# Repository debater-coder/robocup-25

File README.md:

# Robocup 2025

- `./pico/` -- use rshell to copy contents of `./pico/` to the Raspberry Pi Pico running MicroPython
- `./simulator/` -- bevy rust project. Dependencies are listed in `./shell.nix` (excluding rust/cargo)

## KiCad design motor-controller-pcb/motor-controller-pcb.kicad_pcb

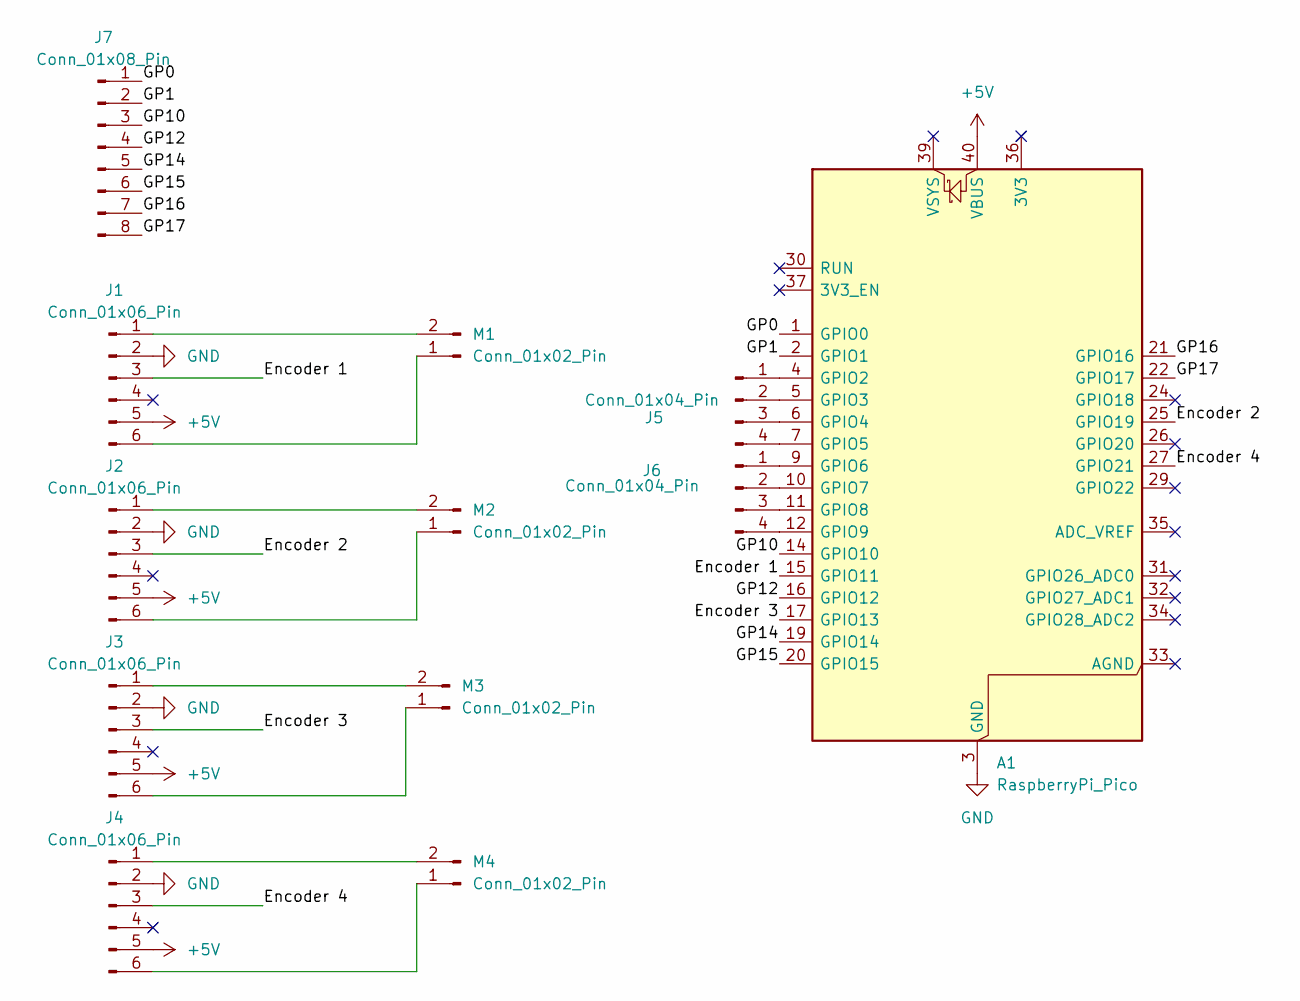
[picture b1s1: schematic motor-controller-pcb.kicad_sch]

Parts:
A1: RaspberryPi_Pico; RaspberryPi_Pico_Common_Unspecified
J1, J2, J3, J4: Conn_01x06_Pin; PinHeader_1x06_P2.54mm_Vertical
J5, J6: Conn_01x04_Pin; PinHeader_1x04_P2.54mm_Vertical
J7: Conn_01x08_Pin; PinHeader_1x08_P2.54mm_Vertical
M1, M2, M3, M4: Conn_01x02_Pin; PinHeader_1x02_P2.54mm_Vertical

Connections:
+5V: A1.40 (VBUS), J1.5, J2.5, J3.5, J4.5
/Encoder 1: A1.15 (GPIO11), J1.3
/Encoder 2: A1.25 (GPIO19), J2.3
/Encoder 3: A1.17 (GPIO13), J3.3
/Encoder 4: A1.27 (GPIO21), J4.3
/GP0: A1.1 (GPIO0), J7.1
/GP1: A1.2 (GPIO1), J7.2
/GP10: A1.14 (GPIO10), J7.3
/GP12: A1.16 (GPIO12), J7.4
/GP14: A1.19 (GPIO14), J7.5
/GP15: A1.20 (GPIO15), J7.6
/GP16: A1.21 (GPIO16), J7.7
/GP17: A1.22 (GPIO17), J7.8
GND: A1.3 (GND), A1.8 (GND), A1.13 (GND), A1.18 (GND), A1.23 (GND), A1.28 (GND), A1.38 (GND), J1.2, J2.2, J3.2, J4.2
unnamed: A1.4 (GPIO2), J5.1
unnamed: A1.5 (GPIO3), J5.2
unnamed: A1.6 (GPIO4), J5.3
unnamed: A1.7 (GPIO5), J5.4
unnamed: A1.9 (GPIO6), J6.1
unnamed: A1.10 (GPIO7), J6.2
unnamed: A1.11 (GPIO8), J6.3
unnamed: A1.12 (GPIO9), J6.4
unnamed: J1.1, M1.2
unnamed: J1.6, M1.1
unnamed: J2.1, M2.2
unnamed: J2.6, M2.1
unnamed: J3.1, M3.2
unnamed: J3.6, M3.1
unnamed: J4.1, M4.2
unnamed: J4.6, M4.1

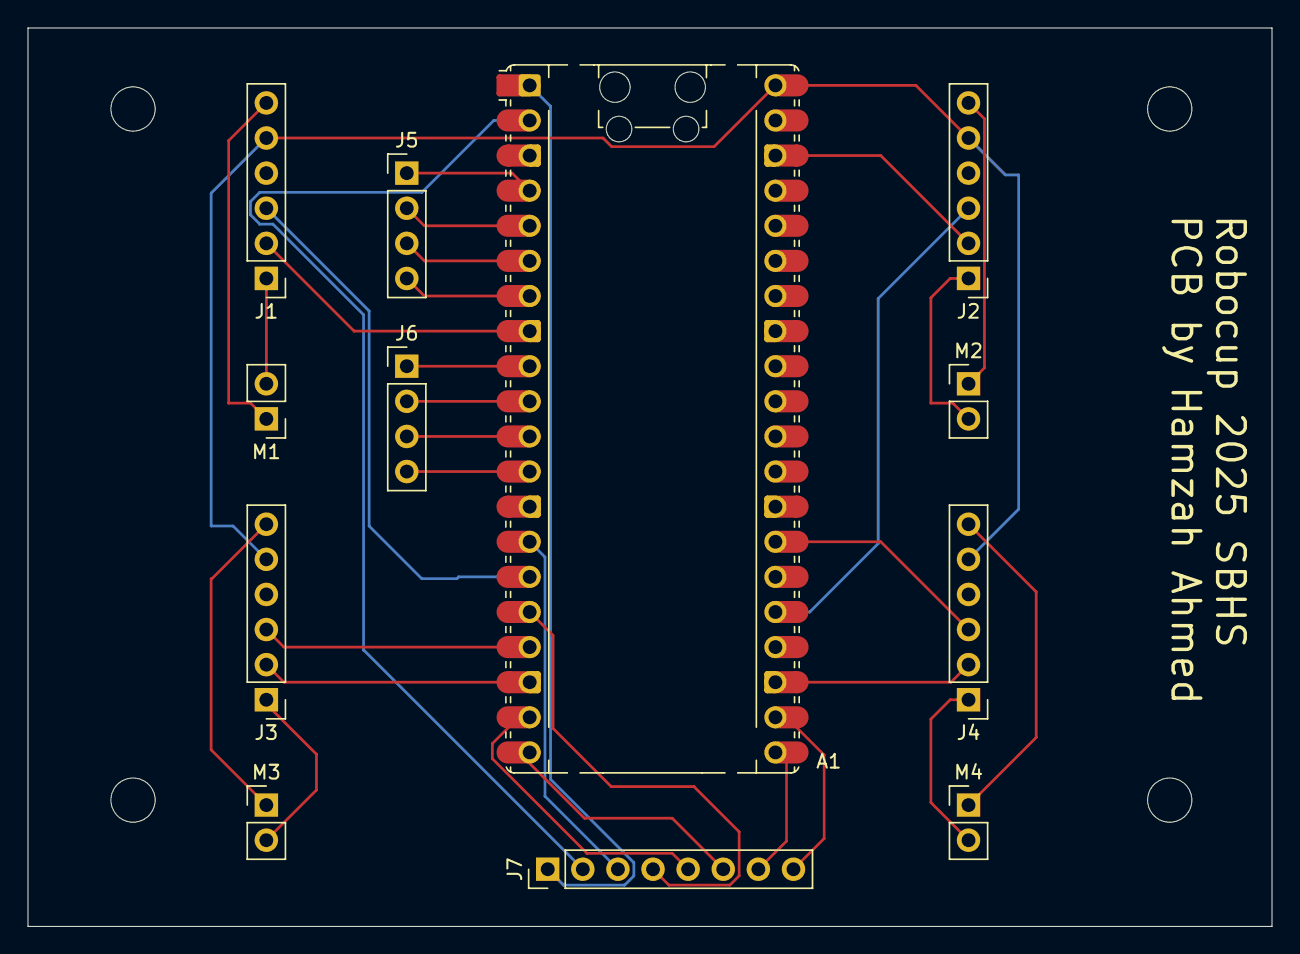
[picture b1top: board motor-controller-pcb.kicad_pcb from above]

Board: 2 copper layers, 90.0 x 65.0 mm, 12 parts (0 on the bottom side), 30 nets.

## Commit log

2024-12-09 good
2024-12-11 update submodules
2024-12-12 start pico again
2025-03-02 simulator stuff
2025-03-12 feat: encoder implementation
2025-03-18 simplify encoder
    Direction measurement was unreliable. Now encoder class doesn't do any
    floating point allocations, and direction is assumed based on motor
    controller polarity.
2025-05-04 Update Robocup_strats.py
    not much
2025-05-04 fix: motor feedback with correctish pins
2025-05-12 remove shell
2025-05-13 fix motors
2025-05-19 working closed loop control
2025-05-20 remove test code
2025-05-20 fix: fix type checking
2025-06-18 encoder distance test
2025-07-03 design pcb
2025-07-04 feat: pcb
2025-07-23 feat: non blocking input on pico
2025-07-23 feat: use command to update kinematics
2025-07-24 fix: correct motor order
2025-07-24 feat: serial output odometry
2025-07-29 fix: calibration constants for odometry
2025-07-29 feat: controller
2025-08-01 feat: initial odometry interface
2025-08-01 feat: serial command and interface
2025-08-03 feat: behaviour trees
2025-08-04 feat: velocity control
2025-08-04 fix: stop motors on termination
    Motors are now stopped on behaviour termination. Additionally, motor
    odometry is initialised in setup() to avoid a large spike in detected
    velocity if odometry starts at something other than (0, 0, 0).
2025-08-05 feat: localisation from odom
2025-08-05 feat: field view
2025-08-05 feat: velocity input
2025-08-11 feat: draw robot
2025-08-12 feat: debug velocity control
2025-08-12 feat: send velocity control
2025-08-13 feat: /pose websocket
2025-08-13 feat: stream pose data over websockets
2025-08-19 feat: motors match pcb
2025-08-19 fix: better p control
2025-08-19 fix: handle serial resetting and dont repeat commands
2025-08-19 fix: correct localisation from naive odom
    - odom naievely adds x, y, w values together without considering frame
    of reference
    - should actually consider pre-existing rotation of robot when adding
    robot's x, y values
    - now correction is done by considering delta as an approximation
    - simulator now has correct origin and displays these from the
2025-08-19 fix: move serial command to different process
    - it tend to hang a little, so moving to another process
    helps to not block the main queue
    - with the non-blocking IO before, writes were overwhelming MCU, this
    allows for MCU to block before sending command again
2025-08-20 fix: proper import
2025-08-20 fix: read after writing
2025-08-20 fix: hack to read a lot after writing
2025-08-20 feat: actually call the funciton
2025-08-20 fix: tune pid
2025-08-21 feat: velocity chart
2025-08-21 feat: serial command instrumentation
2025-08-21 feat: ball detection
2025-08-21 fix: cv libs
2025-08-21 backup old changes
2025-08-24 feat: test motors connect top pi
2025-08-24 feat: move motors off i2c
2025-08-24 feat: pi command
2025-08-25 fix: correct gpio
2025-08-25 feat: basic strategy to go to ball
2025-08-25 feat: smth
2025-08-26 feat: things
2025-08-26 something
2025-09-09 build(deps-dev): bump vite from 7.0.6 to 7.0.7 in /debug-ui
    Bumps [vite](https://github.com/vitejs/vite/tree/HEAD/packages/vite) from 7.0.6 to 7.0.7.
    - [Release notes](https://github.com/vitejs/vite/releases)
    - [Changelog](https://github.com/vitejs/vite/blob/v7.0.7/packages/vite/CHANGELOG.md)
    - [Commits](https://github.com/vitejs/vite/commits/v7.0.7/packages/vite)
    ---
    updated-dependencies:
2025-10-20 build(deps-dev): bump vite from 7.0.6 to 7.0.8 in /debug-ui
    Bumps [vite](https://github.com/vitejs/vite/tree/HEAD/packages/vite) from 7.0.6 to 7.0.8.
    - [Release notes](https://github.com/vitejs/vite/releases)
    - [Changelog](https://github.com/vitejs/vite/blob/v7.0.8/packages/vite/CHANGELOG.md)
    - [Commits](https://github.com/vitejs/vite/commits/v7.0.8/packages/vite)
    ---
    updated-dependencies:
2026-04-06 build(deps-dev): bump vite from 7.0.6 to 7.3.2 in /debug-ui
    Bumps [vite](https://github.com/vitejs/vite/tree/HEAD/packages/vite) from 7.0.6 to 7.3.2.
    - [Release notes](https://github.com/vitejs/vite/releases)
    - [Changelog](https://github.com/vitejs/vite/blob/v7.3.2/packages/vite/CHANGELOG.md)
    - [Commits](https://github.com/vitejs/vite/commits/v7.3.2/packages/vite)
    ---
    updated-dependencies:
